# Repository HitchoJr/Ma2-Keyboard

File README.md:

# Ma2-Keyboard
 Ma2 light Keyboard

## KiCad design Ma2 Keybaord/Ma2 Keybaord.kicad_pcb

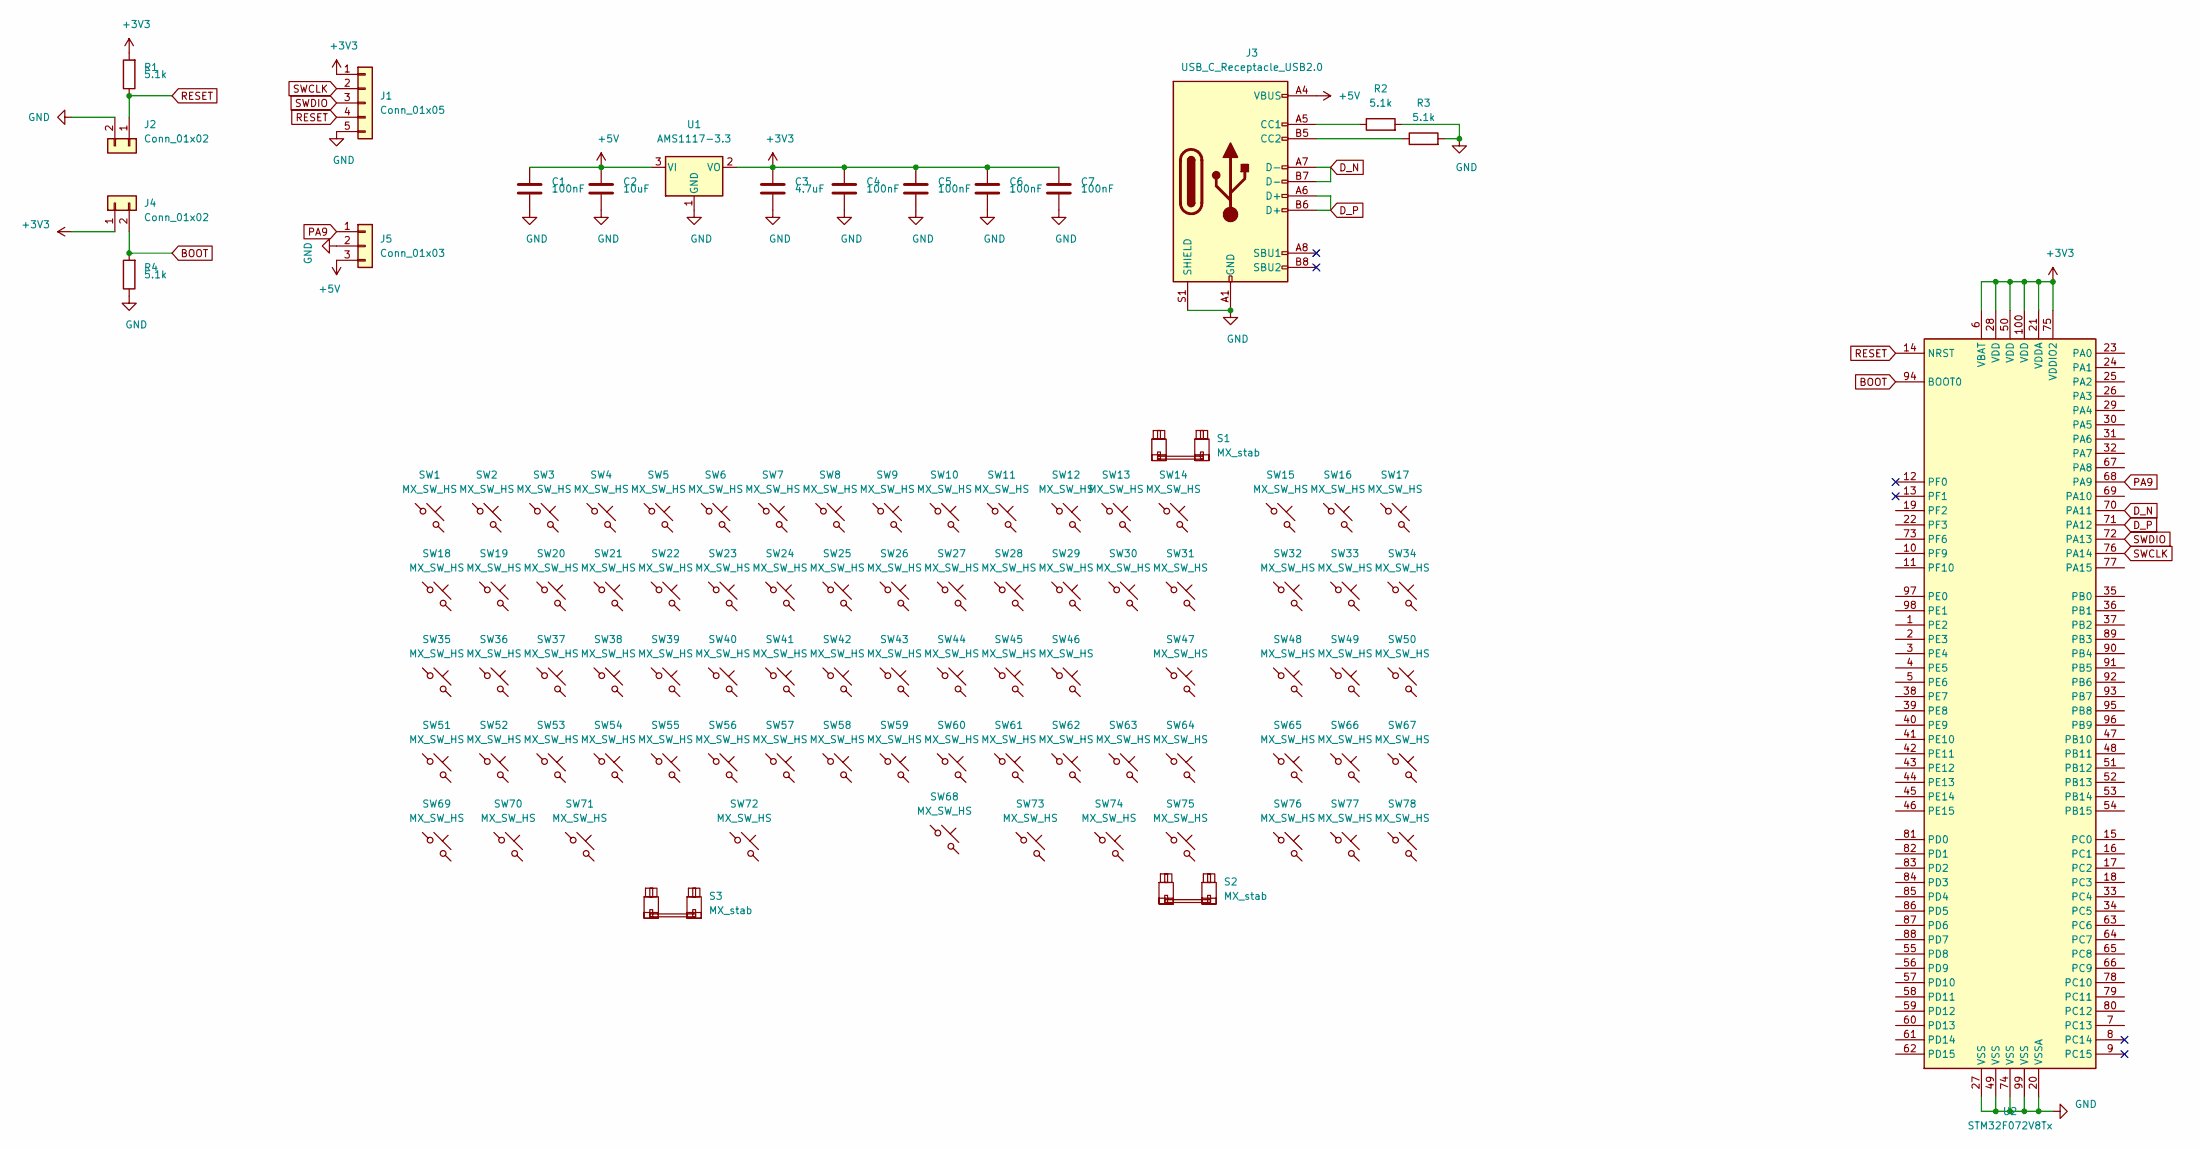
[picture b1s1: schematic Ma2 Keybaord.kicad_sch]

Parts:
C1, C4, C5, C6, C7: 100nF; C_0603_1608Metric
C2: 10uF; C_0603_1608Metric
C3: 4.7uF; C_0603_1608Metric
J1: Conn_01x05; PinHeader_1x05_P2.54mm_Vertical
J2, J4: Conn_01x02; PinHeader_1x02_P2.54mm_Vertical
J3: USB_C_Receptacle_USB2.0; U262-161N-4BVC11
J5: Conn_01x03; PinHeader_1x03_P2.54mm_Vertical
R1, R2, R3, R4: 5.1k; R_0603_1608Metric
S1, S2: MX_stab; STAB_MX_P_2u
S3: MX_stab; STAB_MX_P_6u
SW1, SW2, SW3, SW4, SW5, SW6, SW7, SW8, SW9, SW10, SW11, SW12, SW13, SW14, SW15, SW16, SW17, SW19, SW20, SW21, SW22, SW23, SW24, SW25, SW26, SW27, SW28, SW29, SW30, SW32, SW33, SW34, SW36, SW37, SW38, SW39, SW40, SW41, SW42, SW43, SW44, SW45, SW46, SW47, SW48, SW49, SW50, SW51, SW52, SW53, SW54, SW55, SW56, SW57, SW58, SW59, SW60, SW61, SW62, SW63, SW64, SW65, SW66, SW67, SW68, SW69, SW70, SW71, SW72, SW73, SW74, SW75, SW76, SW77, SW78: MX_SW_HS; SW_MX_HS_1u
SW18, SW31: MX_SW_HS; SW_MX_HS_1.5u
SW35: MX_SW_HS; SW_MX_HS_1.75u_stp
U1: AMS1117-3.3; SOT-223-3_TabPin2
U2: STM32F072V8Tx; LQFP-100_14x14mm_P0.5mm

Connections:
+3V3: C3.1, C4.1, C5.1, C6.1, C7.1, J1.1, J4.1, R1.2, U1.2 (VO), U2.6 (VBAT), U2.21 (VDDA), U2.28 (VDD), U2.50 (VDD), U2.75 (VDDIO2), U2.100 (VDD)
+5V: C1.1, C2.1, J3.A4 (VBUS), J3.A9 (VBUS), J3.B4 (VBUS), J3.B9 (VBUS), J5.3, U1.3 (VI)
BOOT: J4.2, R4.2, U2.94 (BOOT0)
D_N: J3.A7 (D-), J3.B7 (D-), U2.70 (PA11)
D_P: J3.A6 (D+), J3.B6 (D+), U2.71 (PA12)
GND: C1.2, C2.2, C3.2, C4.2, C5.2, C6.2, C7.2, J1.5, J2.2, J3.A1 (GND), J3.A12 (GND), J3.B1 (GND), J3.B12 (GND), J3.S1 (SHIELD), J5.2, R2.2, R3.2, R4.1, U1.1 (GND), U2.20 (VSSA), U2.27 (VSS), U2.49 (VSS), U2.74 (VSS), U2.99 (VSS)
unnamed: J3.A5 (CC1), R2.1
unnamed: J3.B5 (CC2), R3.1
PA9: J5.1, U2.68 (PA9)
RESET: J1.4, J2.1, R1.1, U2.14 (NRST)
SWCLK: J1.2, U2.76 (PA14)
SWDIO: J1.3, U2.72 (PA13)

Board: 2 copper layers, 98 parts (9 on the bottom side), 8 nets, no tracks yet.

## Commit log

2023-01-17 Ma2 V1
    the first of many
2023-01-17 v1.1
2023-01-17 Add submodules
2023-01-17 V1.2
2023-01-20 v1.3
2023-01-31 more work on the keyboard lay out on the PCB also making 4.5U stab
